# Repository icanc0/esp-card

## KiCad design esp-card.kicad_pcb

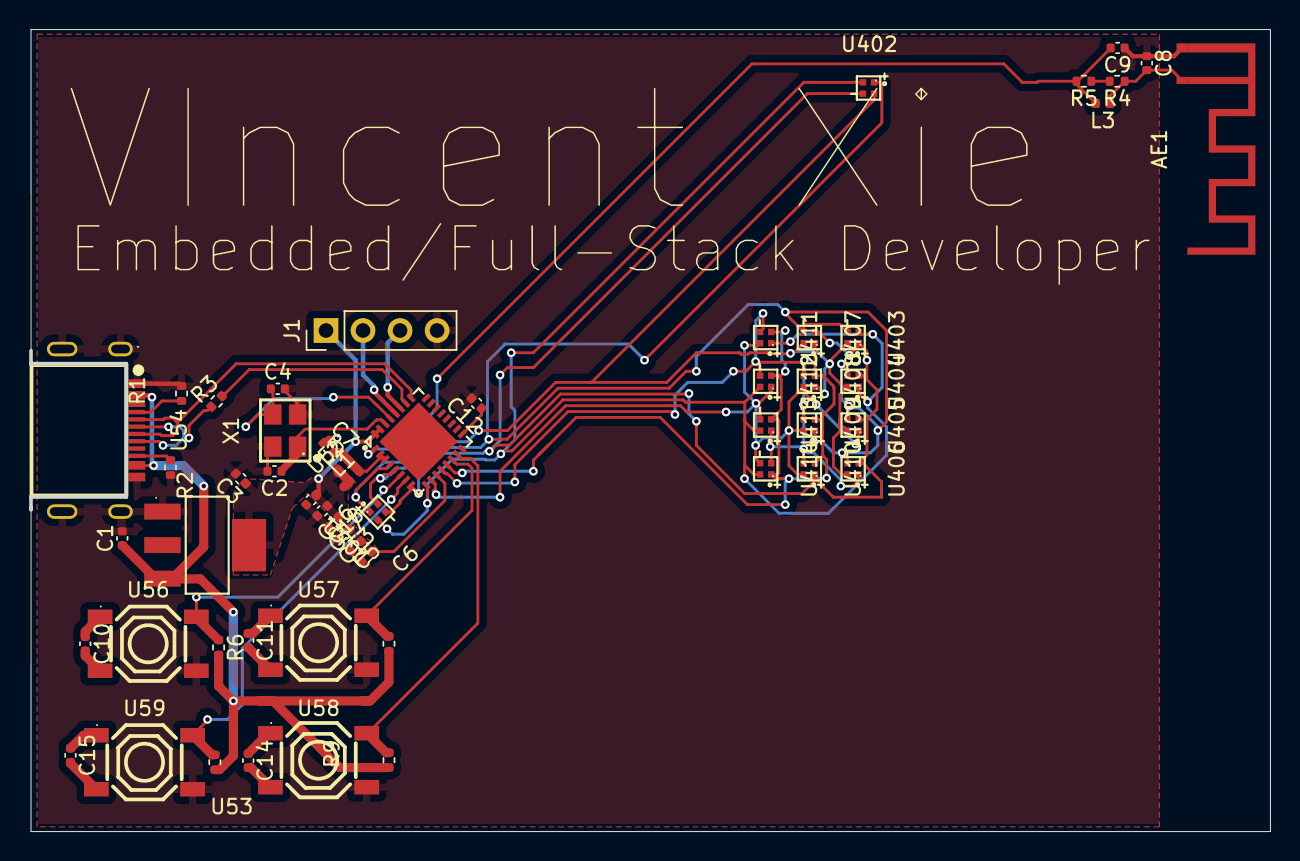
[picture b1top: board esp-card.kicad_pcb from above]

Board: 2 copper layers, 84.9 x 54.8 mm, 54 parts (0 on the bottom side), 35 nets.

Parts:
AE1: Antenna; ESPRESSIF_ESP32_MIFA_2.4GHz_Right
C1, C3, C12, C17: 1uF; C_0402_1005Metric
C2, C4: 12pF; C_0402_1005Metric
C5, C18: 2.2uF; C_0402_1005Metric
C6, C7, C10, C11, C13, C15, C16: 100nF; C_0402_1005Metric
C8, C9: 2pF; C_0402_1005Metric
C14: 10pF; C_0402_1005Metric
J1: Conn_01x04_Socket; PinHeader_1x04_P2.54mm_Vertical
L1, L2: 3.9nH; L_0402_1005Metric
L3: 2.2nH; L_0402_1005Metric
R1, R2: 5.1k; R_0402_1005Metric
R3: 1.5k; R_0402_1005Metric
R4, R5: 0; R_0402_1005Metric
R6, R7, R8, R9: 10k; R_0402_1005Metric
U53: AMS1117-3_3; SOT-223-3_L6.5-W3.4-P2.30-LS7.0-BR
U54: YTC-TC16-30; USB-C-SMD_YIYUAN_YTC-TC16-30
U55: ESP32-C3FH4; QFN-32_L5.0-W5.0-P0.50-TL-EP3.7
U56, U57, U58, U59: TS-1187A-B-A-B; SW-SMD_4P-L5.1-W5.1-P3.70-LS6.5-TL-2
U401, U402, U403, U404, U405, U406, U407, U408, U409, U410, U411, U412, U413, U414: NH-B1010RGBT-HF; LED-ARRAY-SMD_4P-L1.0-W1.0-TR_NH-B1010RGBT
X1: CF4040M00015001; CRYSTAL-SMD_4P-L3.2-W2.5-BL_SIT8008BI

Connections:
+3.3V: C3.1, C5.1, C6.1, C12.1, C13.1, C16.1, C17.1, C18.1, J1.1, L1.1, L2.1, U53.4 (VOUT), U55.11 (VDD3P3_RTC), U55.17 (VDD3P3_CPU), U55.31 (VDDA), U55.32 (VDDA)
+5V: C1.1, R6.2, R7.2, R8.2, R9.2, U53.3 (VIN), U54.A4-B9 (VBUS), U54.B4-A9 (VBUS)
/LED_Matrix_7_pin/CTRL0: U55.4 (XTAL_32K_P), U401.1 (+), U402.2 (-), U403.2 (-), U404.2 (-), U405.2 (-), U406.2 (-), U407.2 (-), U408.1 (+)
/LED_Matrix_7_pin/CTRL1: U55.5 (XTAL_32K_N), U401.2 (-), U402.1 (+), U403.3 (-), U404.3 (-), U405.3 (-), U406.3 (-), U407.3 (-), U409.1 (+)
/LED_Matrix_7_pin/CTRL2: U55.8 (GPIO3), U401.3 (-), U402.3 (-), U403.1 (+), U404.4 (-), U405.4 (-), U406.4 (-), U407.4 (-), U410.1 (+)
/LED_Matrix_7_pin/CTRL3: U55.9 (MTMS), U401.4 (-), U402.4 (-), U403.4 (-), U404.1 (+), U411.1 (+), U412.2 (-), U413.2 (-), U414.2 (-)
/LED_Matrix_7_pin/CTRL4: U55.10 (MTDI), U405.1 (+), U408.2 (-), U409.2 (-), U410.2 (-), U411.2 (-), U412.1 (+), U413.3 (-), U414.3 (-)
/LED_Matrix_7_pin/CTRL5: U55.12 (MTCK), U406.1 (+), U408.3 (-), U409.3 (-), U410.3 (-), U411.3 (-), U412.3 (-), U413.1 (+), U414.4 (-)
/LED_Matrix_7_pin/CTRL6: U55.13 (MTDO), U407.1 (+), U408.4 (-), U409.4 (-), U410.4 (-), U411.4 (-), U412.4 (-), U413.4 (-), U414.1 (+)
ANT: C9.2, L3.2, R5.2, U55.1 (LNA_IN)
EN: R9.1, U55.7 (CHIP_EN), U59.2 (B)
GND: AE1.2 (Shield), C1.2, C2.2, C3.2, C4.2, C5.2, C6.2, C7.2, C8.1, C9.1, C12.2, C13.2, C16.2, C17.2, C18.2, J1.4, R1.2, R2.2, U53.1 (GND), U54.1 (SHELL), U54.2 (SHELL), U54.3 (SHELL), U54.4 (SHELL), U54.A1-B12 (GND), U54.B1-A12 (GND), U55.33 (EP), U56.4 (D), U57.4 (D), U58.4 (D), U59.4 (D), X1.2 (GND), X1.4 (GND)
GPIO2: R6.1, U55.6 (GPIO2), U56.2 (B)
GPIO8: R7.1, U55.14 (GPIO8), U57.2 (B)
GPIO9: R8.1, U55.15 (GPIO9), U58.2 (B)
unnamed: AE1.1 (A), C8.2, L3.1, R4.1
unnamed: C7.1, L1.2, L2.2, U55.2 (VDD3P3), U55.3 (VDD3P3)
unnamed: R4.2, R5.1
unnamed: R1.1, U54.A5 (CC1)
unnamed: R2.1, U54.B5 (CC2)
unnamed: R3.1, U54.A6 (DP1), U54.B6 (DP2)
unnamed: C10.1, U56.1 (A)
unnamed: C10.2, U56.3 (C)
unnamed: C11.1, U57.1 (A)
unnamed: C11.2, U57.3 (C)
unnamed: C14.1, U58.1 (A)
unnamed: C14.2, U58.3 (C)
unnamed: C15.1, U59.1 (A)
unnamed: C15.2, U59.3 (C)
UART_0_RX: J1.3, U55.27 (U0RXD)
UART_0_TX: J1.2, U55.28 (U0TXD)
USB_N: U54.A7 (DN1), U54.B7 (DN2), U55.25 (GPIO18)
USB_PU: R3.2, U55.26 (GPIO19)
XIN: C2.1, U55.30 (XTAL_P), X1.1
XOUT: C4.1, U55.29 (XTAL_N), X1.3

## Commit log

2024-03-15 project setup
2024-03-15 added symbols
2024-03-15 Set up kicad project
2024-03-15 Remove redundant kicad project
2024-03-15 Create schematic skeleton
2024-03-15 Add schematic pdf Github Action
2024-03-15 Fix accidental connection of D+ and VBUS
2024-03-15 Hook up clock, UART
2024-03-17 added labels and figured out RGB charlieplexing
2024-03-18 feat: led matrix placed
2024-03-18 feat: led matrix wiring finished
2024-03-18 led matrix cleanup
2024-03-18 fix: led matrix clean up with bus notation
2024-03-18 fix: corrected labels and hierarchy
2024-03-18 fixed project footprint lib
2024-03-19 Update gitignore
2024-03-19 Finish wiring up ESP basics
2024-03-19 Swap USB and LDO
2024-03-19 Break out remaining GPIO to labels, change UART to 1x4
2024-03-19 Drop files from .gitignore
2024-03-19 symbol fixes + placement
2024-03-19 Add PB_2, PB_8, switch antenna symbol to antenna shield
2024-03-21 updated sheet
2024-03-25 fixed LED matrix
2024-03-28 better routing
2024-03-30 fixed routing
2024-03-30 antenna footprint fix
2024-03-31 finished up routing
2024-03-31 added models
2024-03-31 DRC checks
2024-04-01 made final changes
